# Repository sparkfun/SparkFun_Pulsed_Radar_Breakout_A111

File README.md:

SparkFun Pulsed Radar Breakout - A111
========================================

[*SparkFun A111 Pulsed Radar (SEN-16826)*](https://www.sparkfun.com/products/16826)

Does your project require high-precision, cutting-edge distance measurement? Or maybe speed-, motion-, or gesture-sensing? We’re not talking about simple ultrasonic, or even infrared, sensors here, but 60GHz radar! Well say hello to our tiny, pulsed-radar friend: the Acconeer A111.

The A111 is a single-chip solution for pulsed coherent radar (PCR). It comes complete with integrated antennae and an SPI interface capable of clock speeds of up to 50MHz. The A111’s primary use case is distance-sensing, but it also supports applications in gesture-, motion-, material-, and speed-detection. It can see objects at distances of up to two meters.

Our breakout board for the A111 includes a 1.8V regulator, voltage-level translation between 1.8V and 5V, and, of course, it breaks out all pins of the pulsed radar sensor to both 0.1-inch and Raspberry Pi-friendly headers.

The breakout board is primarily **designed to interface directly with a Raspberry Pi** – Acconeer’s SDK currently only supports ARMv7’s (e.g. a Pi) and ARM Cortex-M4’s. Check out our <a href="https://learn.sparkfun.com/tutorials/getting-started-with-the-a111-pulsed-radar-sensor">Getting Started with the A111 Pulsed Radar Sensor tutorial</a>, which explains how to use the sensor with a Raspberry Pi.

SparkFun labored with love to create this board. Feel like supporting open source hardware? 
Buy a [breakout board](https://www.sparkfun.com/products/16826) from SparkFun!

Repository Contents
-------------------

* **/Documents** - Datasheets
* **/Hardware** - Eagle design files (.brd, .sch)
* **/Production** - Production panel files (.brd)

Documentation
-------------------
* Acconeer
  * **[Developer](https://developer.acconeer.com/)** - SW Download, datasheet, user guide, FAQ
* **[Acconeer Example Code](https://github.com/acconeer)**
* **[Example Code](https://github.com/sparkfun/SparkFun_Pulsed_Radar_A111_Example_Code)** - Archived repo that used to hold the SparkFun example code for the Pulsed Radar Breakout. Make sure to head over to Acconeer's website to download the latest! 
* **[Getting Started Guide](https://learn.sparkfun.com/tutorials/getting-started-with-the-a111-pulsed-radar-sensor)** - Basic hookup guide.

Product Versions
----------------
* [SEN-16826](https://www.sparkfun.com/products/16826) - v1.1
* [SEN-15577](https://www.sparkfun.com/products/15577) - v1.0

Version History
---------------
- v1.1
- [v1.0](https://github.com/sparkfun/SparkFun_Pulsed_Radar_Breakout_A111/releases/tag/v1.0) - initial release

License Information
-------------------

This product is _**open source**_! 

If you have any questions or concerns on licensing, please contact technical support on our [SparkFun forums](https://forum.sparkfun.com/viewforum.php?f=152).

Please use, reuse, and modify these files as you see fit. Please maintain attribution to SparkFun Electronics and release any derivative under the same license.

Distributed as-is; no warranty is given.

- Your friends at SparkFun.

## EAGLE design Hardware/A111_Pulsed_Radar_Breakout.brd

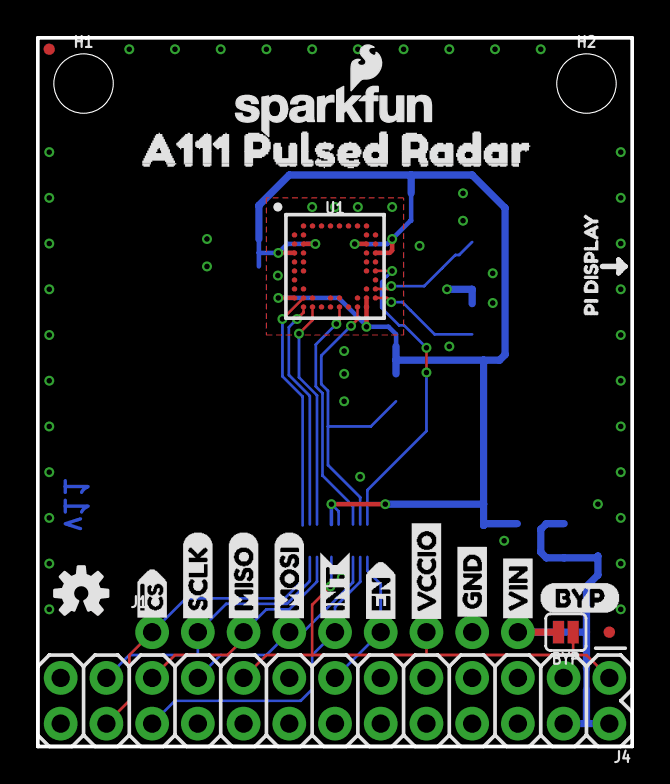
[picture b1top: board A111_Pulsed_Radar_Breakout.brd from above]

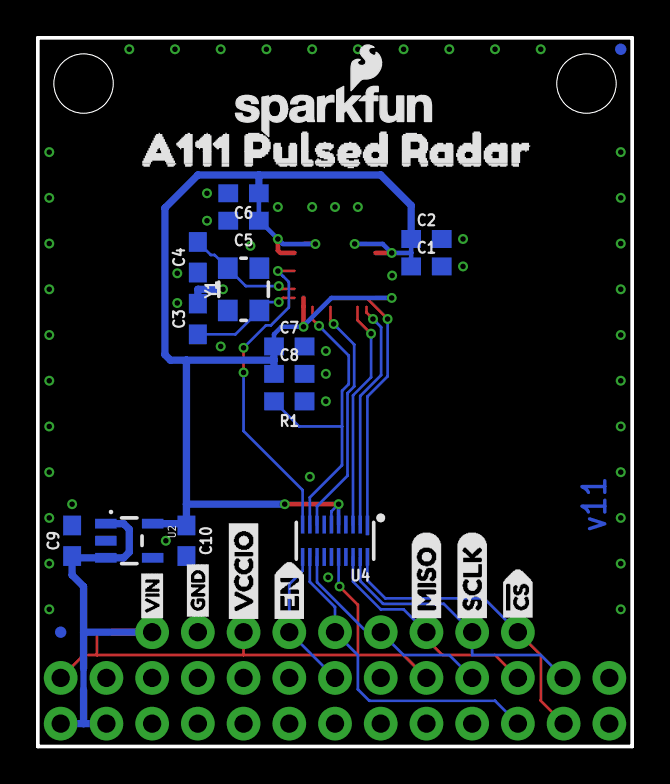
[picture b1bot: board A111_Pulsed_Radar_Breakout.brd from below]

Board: 2 copper layers, 33.0 x 39.4 mm, 48 parts (25 on the bottom side), 18 nets.

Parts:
BYP: JUMPER-SMT_2_NO_SILK; SMT-JUMPER_2_NO_SILK
C1, C5, C7: 0.1uF; 0603
C2, C6, C8, C9, C10: 1.0uF; 0603
C3, C4: 10pF; 0603
FD1, FD2, FD3, FD4: FIDUCIALUFIDUCIAL; FIDUCIAL-MICRO
FRAME1: FRAME-LETTER; CREATIVE_COMMONS
H1, H2: STAND-OFF
J1: 1X09_NO_SILK
J4: RASPBERRYPI-26-PIN-GPIO; 2X13
LOGO1, LOGO3: SFE_LOGO_NAME_FLAME.1_INCH; SFE_LOGO_NAME_FLAME_.1
LOGO2: OSHW-LOGOS; OSHW-LOGO-S
R1: 100k; 0603
U1: A111
U2: AP2127K-1.8V; SOT23-5
U4: TXB0108DQSR; UFDFN-20
U$1, U$9: A111_PULSED_RADAR9
U$2, U$10: SCLK3
U$3, U$11: MISO4
U$4: MOSI5
U$5: INT8
U$6, U$18: EN9
U$7: GND0
U$8: BYP
U$12: PI_DISPLAY9
U$13, U$17: #CS9
U$16: VIN0
U$19, U$20: VCCIO1
U$21: GND6
U$22: VIN5
Y1: 26MHz; CRYSTAL-SMD-3.2X2.5MM

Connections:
1.8V: C1.1, C2.1, C5.1, C6.1, C7.1, C8.1, C10.1, U1.C2, U1.C9, U1.D1, U1.D10, U1.J1, U1.J9, U1.K9, U2.5, U4.5, U4.6
!CS!: U1.J2, U4.1
!CS!_RPI: J1.1, J4.24, U4.20
ENABLE: U1.F10, U4.10
ENABLE_RPI: J1.6, J4.13, U4.11
GND: C1.2, C2.2, C3.2, C4.1, C5.2, C6.2, C7.2, C8.2, C9.2, C10.2, J1.8, J4.6, J4.9, J4.14, J4.20, J4.25, R1.1, U1.A3, U1.A4, U1.A5, U1.A6, U1.A7, U1.A8, U1.A9, U1.B2, U1.B9, U1.B10, U1.C1, U1.C10, U1.D2, U1.D9, U1.E1, U1.E2, U1.E9, U1.E10, U1.F1, U1.F2, U1.F9, U1.G1, U1.G10, U1.H1, U1.H2, U1.H9, U1.J3, U1.J5, U1.J6, U1.J8, U1.K4, U1.K5, U1.K7, U2.2, U4.15, Y1.2, Y1.4
INTERRUPT: R1.2, U1.K8, U4.9
INTERRUPT_RPI: J1.5, J4.22, U4.12
MISO: U1.K3, U4.3
MISO_RPI: J1.3, J4.21, U4.18
MOSI: U1.K6, U4.8
MOSI_RPI: J1.4, J4.19, U4.13
unnamed: C3.1, U1.J10, Y1.1
unnamed: C4.2, U1.H10, Y1.3
SCLK: U1.K2, U4.2
SCLK_RPI: J1.2, J4.23, U4.19
VCCIO: BYP.1, J1.7, J4.1, J4.17, U4.16
VIN: BYP.2, C9.1, J1.9, J4.2, J4.4, U2.1, U2.3

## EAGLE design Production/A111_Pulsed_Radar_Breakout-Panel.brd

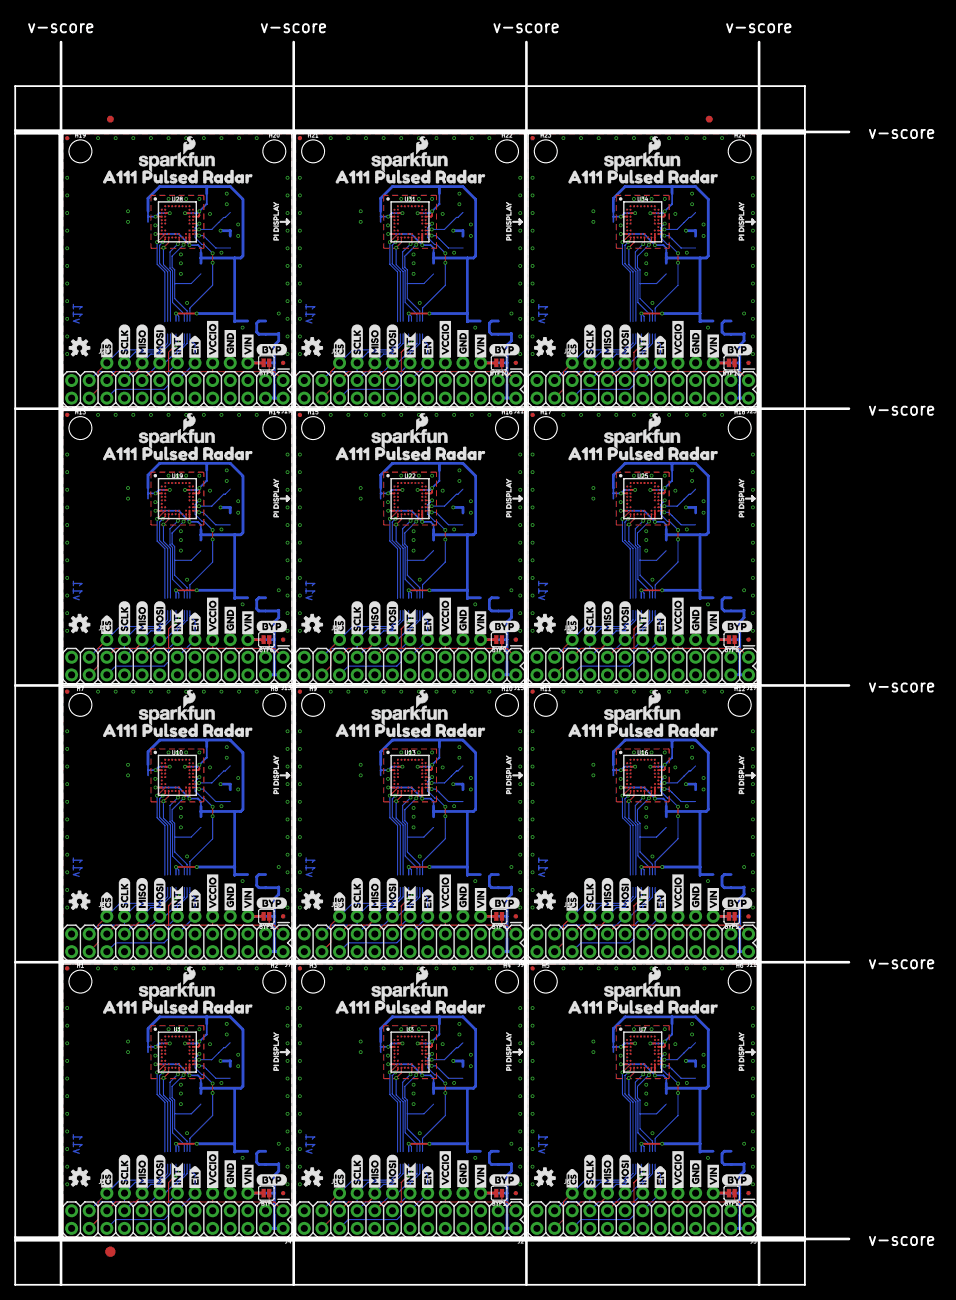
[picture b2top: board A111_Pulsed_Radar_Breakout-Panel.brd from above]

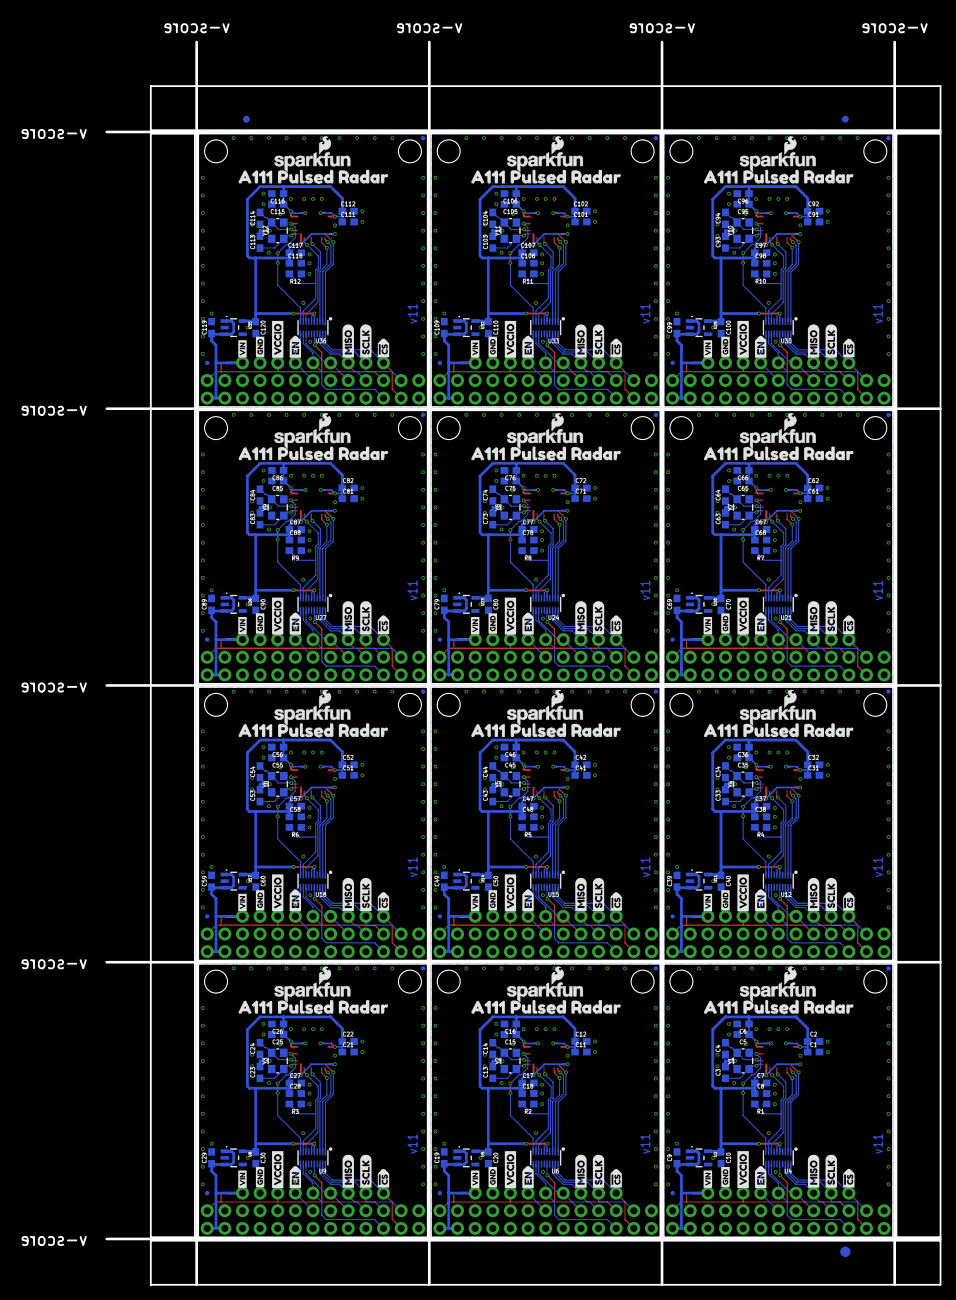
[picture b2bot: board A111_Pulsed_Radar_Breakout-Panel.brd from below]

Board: 2 copper layers, 133.3 x 182.9 mm, 570 parts (303 on the bottom side), 216 nets.

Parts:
BYP, BYP1, BYP2, BYP3, BYP4, BYP5, BYP6, BYP7, BYP8, BYP9, BYP10, BYP11: JUMPER-SMT_2_NO_SILK; SMT-JUMPER_2_NO_SILK
C1, C5, C7, C11, C15, C17, C21, C25, C27, C31, C35, C37, C41, C45, C47, C51, C55, C57, C61, C65, C67, C71, C75, C77, C81, C85, C87, C91, C95, C97, C101, C105, C107, C111, C115, C117: 0.1uF; 0603
C2, C6, C8, C9, C10, C12, C16, C18, C19, C20, C22, C26, C28, C29, C30, C32, C36, C38, C39, C40, C42, C46, C48, C49, C50, C52, C56, C58, C59, C60, C62, C66, C68, C69, C70, C72, C76, C78, C79, C80, C82, C86, C88, C89, C90, C92, C96, C98, C99, C100, C102, C106, C108, C109, C110, C112, C116, C118, C119, C120: 1.0uF; 0603
C3, C4, C13, C14, C23, C24, C33, C34, C43, C44, C53, C54, C63, C64, C73, C74, C83, C84, C93, C94, C103, C104, C113, C114: 10pF; 0603
E$1, E$2, E$3, E$4: FIDUCIAL-1X2
E$5, E$6: FIDUCIAL-1.5X3
FD1, FD2, FD3, FD4, FD5, FD6, FD7, FD8, FD9, FD10, FD11, FD12, FD13, FD14, FD15, FD16, FD17, FD18, FD19, FD20, FD21, FD22, FD23, FD24, FD25, FD26, FD27, FD28, FD29, FD30, FD31, FD32, FD33, FD34, FD35, FD36, FD37, FD38, FD39, FD40, FD41, FD42, FD43, FD44, FD45, FD46, FD47, FD48: FIDUCIALUFIDUCIAL; FIDUCIAL-MICRO
H1, H2, H3, H4, H5, H6, H7, H8, H9, H10, H11, H12, H13, H14, H15, H16, H17, H18, H19, H20, H21, H22, H23, H24: STAND-OFF
J1, J3, J6, J8, J10, J12, J14, J16, J18, J20, J22, J24: 1X09_NO_SILK
J2, J4, J5, J7, J9, J11, J13, J15, J17, J19, J21, J23: RASPBERRYPI-26-PIN-GPIO; 2X13
LOGO1, LOGO3, LOGO5, LOGO6, LOGO8, LOGO9, LOGO11, LOGO12, LOGO14, LOGO15, LOGO17, LOGO18, LOGO20, LOGO21, LOGO23, LOGO24, LOGO26, LOGO27, LOGO29, LOGO30, LOGO32, LOGO33, LOGO35, LOGO36: SFE_LOGO_NAME_FLAME.1_INCH; SFE_LOGO_NAME_FLAME_.1
LOGO2, LOGO4, LOGO7, LOGO10, LOGO13, LOGO16, LOGO19, LOGO22, LOGO25, LOGO28, LOGO31, LOGO34: OSHW-LOGOS; OSHW-LOGO-S
R1, R2, R3, R4, R5, R6, R7, R8, R9, R10, R11, R12: 100k; 0603
U1, U3, U7, U10, U13, U16, U19, U22, U25, U28, U31, U34: A111
U2, U5, U8, U11, U14, U17, U20, U23, U26, U29, U32, U35: AP2127K-1.8V; SOT23-5
U4, U6, U9, U12, U15, U18, U21, U24, U27, U30, U33, U36: TXB0108DQSR; UFDFN-20
U$1, U$9, U$29, U$30, U$49, U$50, U$69, U$70, U$89, U$90, U$109, U$110, U$129, U$130, U$149, U$150, U$169, U$170, U$189, U$190, U$209, U$210, U$229, U$230: A111_PULSED_RADAR9
U$2, U$10, U$14, U$26, U$41, U$46, U$61, U$66, U$81, U$86, U$101, U$106, U$121, U$126, U$141, U$146, U$161, U$166, U$181, U$186, U$201, U$206, U$221, U$226: SCLK3
U$3, U$11, U$15, U$27, U$42, U$47, U$62, U$67, U$82, U$87, U$102, U$107, U$122, U$127, U$142, U$147, U$162, U$167, U$182, U$187, U$202, U$207, U$222, U$227: MISO4
U$4, U$23, U$43, U$63, U$83, U$103, U$123, U$143, U$163, U$183, U$203, U$223: MOSI5
U$5, U$24, U$44, U$64, U$84, U$104, U$124, U$144, U$164, U$184, U$204, U$224: INT8
U$6, U$18, U$33, U$34, U$53, U$54, U$73, U$74, U$93, U$94, U$113, U$114, U$133, U$134, U$153, U$154, U$173, U$174, U$193, U$194, U$213, U$214, U$233, U$234: EN9
U$7, U$25, U$45, U$65, U$85, U$105, U$125, U$145, U$165, U$185, U$205, U$225: GND0
U$8, U$35, U$55, U$75, U$95, U$115, U$135, U$155, U$175, U$195, U$215, U$235: BYP
U$12, U$31, U$51, U$71, U$91, U$111, U$131, U$151, U$171, U$191, U$211, U$231: PI_DISPLAY9
U$13, U$17, U$28, U$32, U$48, U$52, U$68, U$72, U$88, U$92, U$108, U$112, U$128, U$132, U$148, U$152, U$168, U$172, U$188, U$192, U$208, U$212, U$228, U$232: #CS9
U$16, U$36, U$56, U$76, U$96, U$116, U$136, U$156, U$176, U$196, U$216, U$236: VIN0
U$19, U$20, U$37, U$38, U$57, U$58, U$77, U$78, U$97, U$98, U$117, U$118, U$137, U$138, U$157, U$158, U$177, U$178, U$197, U$198, U$217, U$218, U$237, U$238: VCCIO1
U$21, U$40, U$60, U$80, U$100, U$120, U$140, U$160, U$180, U$200, U$220, U$240: GND6
U$22, U$39, U$59, U$79, U$99, U$119, U$139, U$159, U$179, U$199, U$219, U$239: VIN5
Y1, Y2, Y3, Y4, Y5, Y6, Y7, Y8, Y9, Y10, Y11, Y12: 26MHz; CRYSTAL-SMD-3.2X2.5MM

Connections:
1.8V: C1.1, C2.1, C5.1, C6.1, C7.1, C8.1, C10.1, U1.C2, U1.C9, U1.D1, U1.D10, U1.J1, U1.J9, U1.K9, U2.5, U4.5, U4.6
1.8V1: C11.1, C12.1, C15.1, C16.1, C17.1, C18.1, C20.1, U3.C2, U3.C9, U3.D1, U3.D10, U3.J1, U3.J9, U3.K9, U5.5, U6.5, U6.6
1.8V2: C21.1, C22.1, C25.1, C26.1, C27.1, C28.1, C30.1, U7.C2, U7.C9, U7.D1, U7.D10, U7.J1, U7.J9, U7.K9, U8.5, U9.5, U9.6
1.8V3: C31.1, C32.1, C35.1, C36.1, C37.1, C38.1, C40.1, U10.C2, U10.C9, U10.D1, U10.D10, U10.J1, U10.J9, U10.K9, U11.5, U12.5, U12.6
1.8V4: C41.1, C42.1, C45.1, C46.1, C47.1, C48.1, C50.1, U13.C2, U13.C9, U13.D1, U13.D10, U13.J1, U13.J9, U13.K9, U14.5, U15.5, U15.6
1.8V5: C51.1, C52.1, C55.1, C56.1, C57.1, C58.1, C60.1, U16.C2, U16.C9, U16.D1, U16.D10, U16.J1, U16.J9, U16.K9, U17.5, U18.5, U18.6
1.8V6: C61.1, C62.1, C65.1, C66.1, C67.1, C68.1, C70.1, U19.C2, U19.C9, U19.D1, U19.D10, U19.J1, U19.J9, U19.K9, U20.5, U21.5, U21.6
1.8V7: C71.1, C72.1, C75.1, C76.1, C77.1, C78.1, C80.1, U22.C2, U22.C9, U22.D1, U22.D10, U22.J1, U22.J9, U22.K9, U23.5, U24.5, U24.6
1.8V8: C81.1, C82.1, C85.1, C86.1, C87.1, C88.1, C90.1, U25.C2, U25.C9, U25.D1, U25.D10, U25.J1, U25.J9, U25.K9, U26.5, U27.5, U27.6
1.8V9: C91.1, C92.1, C95.1, C96.1, C97.1, C98.1, C100.1, U28.C2, U28.C9, U28.D1, U28.D10, U28.J1, U28.J9, U28.K9, U29.5, U30.5, U30.6
1.8V10: C101.1, C102.1, C105.1, C106.1, C107.1, C108.1, C110.1, U31.C2, U31.C9, U31.D1, U31.D10, U31.J1, U31.J9, U31.K9, U32.5, U33.5, U33.6
1.8V11: C111.1, C112.1, C115.1, C116.1, C117.1, C118.1, C120.1, U34.C2, U34.C9, U34.D1, U34.D10, U34.J1, U34.J9, U34.K9, U35.5, U36.5, U36.6
!CS!: U1.J2, U4.1
!CS!1: U3.J2, U6.1
!CS!2: U7.J2, U9.1
!CS!3: U10.J2, U12.1
!CS!4: U13.J2, U15.1
!CS!5: U16.J2, U18.1
!CS!6: U19.J2, U21.1
!CS!7: U22.J2, U24.1
!CS!8: U25.J2, U27.1
!CS!9: U28.J2, U30.1
!CS!10: U31.J2, U33.1
!CS!11: U34.J2, U36.1
!CS!_RPI: J1.1, J4.24, U4.20
!CS!_RPI1: J2.24, J3.1, U6.20
!CS!_RPI2: J5.24, J6.1, U9.20
!CS!_RPI3: J7.24, J8.1, U12.20
!CS!_RPI4: J9.24, J10.1, U15.20
!CS!_RPI5: J11.24, J12.1, U18.20
!CS!_RPI6: J13.24, J14.1, U21.20
!CS!_RPI7: J15.24, J16.1, U24.20
!CS!_RPI8: J17.24, J18.1, U27.20
!CS!_RPI9: J19.24, J20.1, U30.20
!CS!_RPI10: J21.24, J22.1, U33.20
!CS!_RPI11: J23.24, J24.1, U36.20
ENABLE: U1.F10, U4.10
ENABLE1: U3.F10, U6.10
ENABLE2: U7.F10, U9.10
ENABLE3: U10.F10, U12.10
ENABLE4: U13.F10, U15.10
ENABLE5: U16.F10, U18.10
ENABLE6: U19.F10, U21.10
ENABLE7: U22.F10, U24.10
ENABLE8: U25.F10, U27.10
ENABLE9: U28.F10, U30.10
ENABLE10: U31.F10, U33.10
ENABLE11: U34.F10, U36.10
ENABLE_RPI: J1.6, J4.13, U4.11
ENABLE_RPI1: J2.13, J3.6, U6.11
ENABLE_RPI2: J5.13, J6.6, U9.11
ENABLE_RPI3: J7.13, J8.6, U12.11
ENABLE_RPI4: J9.13, J10.6, U15.11
ENABLE_RPI5: J11.13, J12.6, U18.11
ENABLE_RPI6: J13.13, J14.6, U21.11
ENABLE_RPI7: J15.13, J16.6, U24.11
ENABLE_RPI8: J17.13, J18.6, U27.11
ENABLE_RPI9: J19.13, J20.6, U30.11
ENABLE_RPI10: J21.13, J22.6, U33.11
ENABLE_RPI11: J23.13, J24.6, U36.11
GND: C1.2, C2.2, C3.2, C4.1, C5.2, C6.2, C7.2, C8.2, C9.2, C10.2, J1.8, J4.6, J4.9, J4.14, J4.20, J4.25, R1.1, U1.A3, U1.A4, U1.A5, U1.A6, U1.A7, U1.A8, U1.A9, U1.B2, U1.B9, U1.B10, U1.C1, U1.C10, U1.D2, U1.D9, U1.E1, U1.E2, U1.E9, U1.E10, U1.F1, U1.F2, U1.F9, U1.G1, U1.G10, U1.H1, U1.H2, U1.H9, U1.J3, U1.J5, U1.J6, U1.J8, U1.K4, U1.K5, U1.K7, U2.2, U4.15, Y1.2, Y1.4
GND1: C11.2, C12.2, C13.2, C14.1, C15.2, C16.2, C17.2, C18.2, C19.2, C20.2, J2.6, J2.9, J2.14, J2.20, J2.25, J3.8, R2.1, U3.A3, U3.A4, U3.A5, U3.A6, U3.A7, U3.A8, U3.A9, U3.B2, U3.B9, U3.B10, U3.C1, U3.C10, U3.D2, U3.D9, U3.E1, U3.E2, U3.E9, U3.E10, U3.F1, U3.F2, U3.F9, U3.G1, U3.G10, U3.H1, U3.H2, U3.H9, U3.J3, U3.J5, U3.J6, U3.J8, U3.K4, U3.K5, U3.K7, U5.2, U6.15, Y2.2, Y2.4
GND2: C21.2, C22.2, C23.2, C24.1, C25.2, C26.2, C27.2, C28.2, C29.2, C30.2, J5.6, J5.9, J5.14, J5.20, J5.25, J6.8, R3.1, U7.A3, U7.A4, U7.A5, U7.A6, U7.A7, U7.A8, U7.A9, U7.B2, U7.B9, U7.B10, U7.C1, U7.C10, U7.D2, U7.D9, U7.E1, U7.E2, U7.E9, U7.E10, U7.F1, U7.F2, U7.F9, U7.G1, U7.G10, U7.H1, U7.H2, U7.H9, U7.J3, U7.J5, U7.J6, U7.J8, U7.K4, U7.K5, U7.K7, U8.2, U9.15, Y3.2, Y3.4
GND3: C31.2, C32.2, C33.2, C34.1, C35.2, C36.2, C37.2, C38.2, C39.2, C40.2, J7.6, J7.9, J7.14, J7.20, J7.25, J8.8, R4.1, U10.A3, U10.A4, U10.A5, U10.A6, U10.A7, U10.A8, U10.A9, U10.B2, U10.B9, U10.B10, U10.C1, U10.C10, U10.D2, U10.D9, U10.E1, U10.E2, U10.E9, U10.E10, U10.F1, U10.F2, U10.F9, U10.G1, U10.G10, U10.H1, U10.H2, U10.H9, U10.J3, U10.J5, U10.J6, U10.J8, U10.K4, U10.K5, U10.K7, U11.2, U12.15, Y4.2, Y4.4
GND4: C41.2, C42.2, C43.2, C44.1, C45.2, C46.2, C47.2, C48.2, C49.2, C50.2, J9.6, J9.9, J9.14, J9.20, J9.25, J10.8, R5.1, U13.A3, U13.A4, U13.A5, U13.A6, U13.A7, U13.A8, U13.A9, U13.B2, U13.B9, U13.B10, U13.C1, U13.C10, U13.D2, U13.D9, U13.E1, U13.E2, U13.E9, U13.E10, U13.F1, U13.F2, U13.F9, U13.G1, U13.G10, U13.H1, U13.H2, U13.H9, U13.J3, U13.J5, U13.J6, U13.J8, U13.K4, U13.K5, U13.K7, U14.2, U15.15, Y5.2, Y5.4
GND5: C51.2, C52.2, C53.2, C54.1, C55.2, C56.2, C57.2, C58.2, C59.2, C60.2, J11.6, J11.9, J11.14, J11.20, J11.25, J12.8, R6.1, U16.A3, U16.A4, U16.A5, U16.A6, U16.A7, U16.A8, U16.A9, U16.B2, U16.B9, U16.B10, U16.C1, U16.C10, U16.D2, U16.D9, U16.E1, U16.E2, U16.E9, U16.E10, U16.F1, U16.F2, U16.F9, U16.G1, U16.G10, U16.H1, U16.H2, U16.H9, U16.J3, U16.J5, U16.J6, U16.J8, U16.K4, U16.K5, U16.K7, U17.2, U18.15, Y6.2, Y6.4
GND6: C61.2, C62.2, C63.2, C64.1, C65.2, C66.2, C67.2, C68.2, C69.2, C70.2, J13.6, J13.9, J13.14, J13.20, J13.25, J14.8, R7.1, U19.A3, U19.A4, U19.A5, U19.A6, U19.A7, U19.A8, U19.A9, U19.B2, U19.B9, U19.B10, U19.C1, U19.C10, U19.D2, U19.D9, U19.E1, U19.E2, U19.E9, U19.E10, U19.F1, U19.F2, U19.F9, U19.G1, U19.G10, U19.H1, U19.H2, U19.H9, U19.J3, U19.J5, U19.J6, U19.J8, U19.K4, U19.K5, U19.K7, U20.2, U21.15, Y7.2, Y7.4
GND7: C71.2, C72.2, C73.2, C74.1, C75.2, C76.2, C77.2, C78.2, C79.2, C80.2, J15.6, J15.9, J15.14, J15.20, J15.25, J16.8, R8.1, U22.A3, U22.A4, U22.A5, U22.A6, U22.A7, U22.A8, U22.A9, U22.B2, U22.B9, U22.B10, U22.C1, U22.C10, U22.D2, U22.D9, U22.E1, U22.E2, U22.E9, U22.E10, U22.F1, U22.F2, U22.F9, U22.G1, U22.G10, U22.H1, U22.H2, U22.H9, U22.J3, U22.J5, U22.J6, U22.J8, U22.K4, U22.K5, U22.K7, U23.2, U24.15, Y8.2, Y8.4
GND8: C81.2, C82.2, C83.2, C84.1, C85.2, C86.2, C87.2, C88.2, C89.2, C90.2, J17.6, J17.9, J17.14, J17.20, J17.25, J18.8, R9.1, U25.A3, U25.A4, U25.A5, U25.A6, U25.A7, U25.A8, U25.A9, U25.B2, U25.B9, U25.B10, U25.C1, U25.C10, U25.D2, U25.D9, U25.E1, U25.E2, U25.E9, U25.E10, U25.F1, U25.F2, U25.F9, U25.G1, U25.G10, U25.H1, U25.H2, U25.H9, U25.J3, U25.J5, U25.J6, U25.J8, U25.K4, U25.K5, U25.K7, U26.2, U27.15, Y9.2, Y9.4
GND9: C91.2, C92.2, C93.2, C94.1, C95.2, C96.2, C97.2, C98.2, C99.2, C100.2, J19.6, J19.9, J19.14, J19.20, J19.25, J20.8, R10.1, U28.A3, U28.A4, U28.A5, U28.A6, U28.A7, U28.A8, U28.A9, U28.B2, U28.B9, U28.B10, U28.C1, U28.C10, U28.D2, U28.D9, U28.E1, U28.E2, U28.E9, U28.E10, U28.F1, U28.F2, U28.F9, U28.G1, U28.G10, U28.H1, U28.H2, U28.H9, U28.J3, U28.J5, U28.J6, U28.J8, U28.K4, U28.K5, U28.K7, U29.2, U30.15, Y10.2, Y10.4
GND10: C101.2, C102.2, C103.2, C104.1, C105.2, C106.2, C107.2, C108.2, C109.2, C110.2, J21.6, J21.9, J21.14, J21.20, J21.25, J22.8, R11.1, U31.A3, U31.A4, U31.A5, U31.A6, U31.A7, U31.A8, U31.A9, U31.B2, U31.B9, U31.B10, U31.C1, U31.C10, U31.D2, U31.D9, U31.E1, U31.E2, U31.E9, U31.E10, U31.F1, U31.F2, U31.F9, U31.G1, U31.G10, U31.H1, U31.H2, U31.H9, U31.J3, U31.J5, U31.J6, U31.J8, U31.K4, U31.K5, U31.K7, U32.2, U33.15, Y11.2, Y11.4
GND11: C111.2, C112.2, C113.2, C114.1, C115.2, C116.2, C117.2, C118.2, C119.2, C120.2, J23.6, J23.9, J23.14, J23.20, J23.25, J24.8, R12.1, U34.A3, U34.A4, U34.A5, U34.A6, U34.A7, U34.A8, U34.A9, U34.B2, U34.B9, U34.B10, U34.C1, U34.C10, U34.D2, U34.D9, U34.E1, U34.E2, U34.E9, U34.E10, U34.F1, U34.F2, U34.F9, U34.G1, U34.G10, U34.H1, U34.H2, U34.H9, U34.J3, U34.J5, U34.J6, U34.J8, U34.K4, U34.K5, U34.K7, U35.2, U36.15, Y12.2, Y12.4
INTERRUPT: R1.2, U1.K8, U4.9
INTERRUPT1: R2.2, U3.K8, U6.9
INTERRUPT2: R3.2, U7.K8, U9.9
INTERRUPT3: R4.2, U10.K8, U12.9
INTERRUPT4: R5.2, U13.K8, U15.9
INTERRUPT5: R6.2, U16.K8, U18.9
INTERRUPT6: R7.2, U19.K8, U21.9
INTERRUPT7: R8.2, U22.K8, U24.9
INTERRUPT8: R9.2, U25.K8, U27.9
INTERRUPT9: R10.2, U28.K8, U30.9
INTERRUPT10: R11.2, U31.K8, U33.9
INTERRUPT11: R12.2, U34.K8, U36.9
INTERRUPT_RPI: J1.5, J4.22, U4.12
INTERRUPT_RPI1: J2.22, J3.5, U6.12
INTERRUPT_RPI2: J5.22, J6.5, U9.12
INTERRUPT_RPI3: J7.22, J8.5, U12.12
INTERRUPT_RPI4: J9.22, J10.5, U15.12
INTERRUPT_RPI5: J11.22, J12.5, U18.12
INTERRUPT_RPI6: J13.22, J14.5, U21.12
INTERRUPT_RPI7: J15.22, J16.5, U24.12
INTERRUPT_RPI8: J17.22, J18.5, U27.12
INTERRUPT_RPI9: J19.22, J20.5, U30.12
INTERRUPT_RPI10: J21.22, J22.5, U33.12
INTERRUPT_RPI11: J23.22, J24.5, U36.12
MISO: U1.K3, U4.3
MISO1: U3.K3, U6.3
MISO2: U7.K3, U9.3
MISO3: U10.K3, U12.3
MISO4: U13.K3, U15.3
MISO5: U16.K3, U18.3
MISO6: U19.K3, U21.3
MISO7: U22.K3, U24.3
MISO8: U25.K3, U27.3
MISO9: U28.K3, U30.3
MISO10: U31.K3, U33.3
MISO11: U34.K3, U36.3
MISO_RPI: J1.3, J4.21, U4.18
MISO_RPI1: J2.21, J3.3, U6.18
MISO_RPI2: J5.21, J6.3, U9.18
MISO_RPI3: J7.21, J8.3, U12.18
MISO_RPI4: J9.21, J10.3, U15.18
MISO_RPI5: J11.21, J12.3, U18.18
MISO_RPI6: J13.21, J14.3, U21.18
MISO_RPI7: J15.21, J16.3, U24.18
MISO_RPI8: J17.21, J18.3, U27.18
MISO_RPI9: J19.21, J20.3, U30.18
MISO_RPI10: J21.21, J22.3, U33.18
MISO_RPI11: J23.21, J24.3, U36.18
MOSI: U1.K6, U4.8
MOSI1: U3.K6, U6.8
MOSI2: U7.K6, U9.8
MOSI3: U10.K6, U12.8
MOSI4: U13.K6, U15.8
MOSI5: U16.K6, U18.8
MOSI6: U19.K6, U21.8
MOSI7: U22.K6, U24.8
MOSI8: U25.K6, U27.8
MOSI9: U28.K6, U30.8
MOSI10: U31.K6, U33.8
MOSI11: U34.K6, U36.8
MOSI_RPI: J1.4, J4.19, U4.13
MOSI_RPI1: J2.19, J3.4, U6.13
MOSI_RPI2: J5.19, J6.4, U9.13
MOSI_RPI3: J7.19, J8.4, U12.13
MOSI_RPI4: J9.19, J10.4, U15.13
MOSI_RPI5: J11.19, J12.4, U18.13
MOSI_RPI6: J13.19, J14.4, U21.13
MOSI_RPI7: J15.19, J16.4, U24.13
MOSI_RPI8: J17.19, J18.4, U27.13
MOSI_RPI9: J19.19, J20.4, U30.13
MOSI_RPI10: J21.19, J22.4, U33.13
MOSI_RPI11: J23.19, J24.4, U36.13
unnamed: C3.1, U1.J10, Y1.1
unnamed: C4.2, U1.H10, Y1.3
unnamed: C13.1, U3.J10, Y2.1
unnamed: C14.2, U3.H10, Y2.3
unnamed: C23.1, U7.J10, Y3.1
unnamed: C24.2, U7.H10, Y3.3
unnamed: C33.1, U10.J10, Y4.1
unnamed: C34.2, U10.H10, Y4.3
unnamed: C43.1, U13.J10, Y5.1
unnamed: C44.2, U13.H10, Y5.3
unnamed: C53.1, U16.J10, Y6.1
unnamed: C54.2, U16.H10, Y6.3
unnamed: C63.1, U19.J10, Y7.1
unnamed: C64.2, U19.H10, Y7.3
unnamed: C73.1, U22.J10, Y8.1
unnamed: C74.2, U22.H10, Y8.3
unnamed: C83.1, U25.J10, Y9.1
unnamed: C84.2, U25.H10, Y9.3
unnamed: C93.1, U28.J10, Y10.1
unnamed: C94.2, U28.H10, Y10.3
unnamed: C103.1, U31.J10, Y11.1
unnamed: C104.2, U31.H10, Y11.3
unnamed: C113.1, U34.J10, Y12.1
unnamed: C114.2, U34.H10, Y12.3
SCLK: U1.K2, U4.2
SCLK1: U3.K2, U6.2
SCLK2: U7.K2, U9.2
SCLK3: U10.K2, U12.2
SCLK4: U13.K2, U15.2
SCLK5: U16.K2, U18.2
SCLK6: U19.K2, U21.2
SCLK7: U22.K2, U24.2
SCLK8: U25.K2, U27.2
SCLK9: U28.K2, U30.2
SCLK10: U31.K2, U33.2
SCLK11: U34.K2, U36.2
SCLK_RPI: J1.2, J4.23, U4.19
SCLK_RPI1: J2.23, J3.2, U6.19
SCLK_RPI2: J5.23, J6.2, U9.19
SCLK_RPI3: J7.23, J8.2, U12.19
SCLK_RPI4: J9.23, J10.2, U15.19
SCLK_RPI5: J11.23, J12.2, U18.19
SCLK_RPI6: J13.23, J14.2, U21.19
SCLK_RPI7: J15.23, J16.2, U24.19
SCLK_RPI8: J17.23, J18.2, U27.19
SCLK_RPI9: J19.23, J20.2, U30.19
SCLK_RPI10: J21.23, J22.2, U33.19
SCLK_RPI11: J23.23, J24.2, U36.19
VCCIO: BYP.1, J1.7, J4.1, J4.17, U4.16
VCCIO1: BYP1.1, J2.1, J2.17, J3.7, U6.16
VCCIO2: BYP2.1, J5.1, J5.17, J6.7, U9.16
VCCIO3: BYP3.1, J7.1, J7.17, J8.7, U12.16
VCCIO4: BYP4.1, J9.1, J9.17, J10.7, U15.16
VCCIO5: BYP5.1, J11.1, J11.17, J12.7, U18.16
VCCIO6: BYP6.1, J13.1, J13.17, J14.7, U21.16
VCCIO7: BYP7.1, J15.1, J15.17, J16.7, U24.16
VCCIO8: BYP8.1, J17.1, J17.17, J18.7, U27.16
VCCIO9: BYP9.1, J19.1, J19.17, J20.7, U30.16
VCCIO10: BYP10.1, J21.1, J21.17, J22.7, U33.16
VCCIO11: BYP11.1, J23.1, J23.17, J24.7, U36.16
VIN: BYP.2, C9.1, J1.9, J4.2, J4.4, U2.1, U2.3
VIN1: BYP1.2, C19.1, J2.2, J2.4, J3.9, U5.1, U5.3
VIN2: BYP2.2, C29.1, J5.2, J5.4, J6.9, U8.1, U8.3
VIN3: BYP3.2, C39.1, J7.2, J7.4, J8.9, U11.1, U11.3
VIN4: BYP4.2, C49.1, J9.2, J9.4, J10.9, U14.1, U14.3
VIN5: BYP5.2, C59.1, J11.2, J11.4, J12.9, U17.1, U17.3
VIN6: BYP6.2, C69.1, J13.2, J13.4, J14.9, U20.1, U20.3
VIN7: BYP7.2, C79.1, J15.2, J15.4, J16.9, U23.1, U23.3
VIN8: BYP8.2, C89.1, J17.2, J17.4, J18.9, U26.1, U26.3
VIN9: BYP9.2, C99.1, J19.2, J19.4, J20.9, U29.1, U29.3
VIN10: BYP10.2, C109.1, J21.2, J21.4, J22.9, U32.1, U32.3
VIN11: BYP11.2, C119.1, J23.2, J23.4, J24.9, U35.1, U35.3

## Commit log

2019-07-30 Updates name in README
2019-08-05 Adds SparkFun logo to the underside, migrates all parts to SparkFun libraries.
2019-08-05 Updates A111 with SKU
2019-08-06 Replaces SparkFun silk with SparkFun silk with flame, grounds, 1.8V voltage regulator
2019-08-08 Changes DRC to SparkFun Fab Limit
2019-08-08 Adds Production Files
2019-08-08 Fixes proportional text in schematic
2019-08-08 Updates schematic with VCC range, updates silk on A111 part
2019-08-08 Updates silk once more
2019-08-08 Repanelizes after silk change
2019-09-24 Board Dimensions
    - Update measures layer
    - Include board dimensions
2019-12-20 Update README.md
    The logic level converter is tied directly to 5V
2020-05-06 Remove Examples
    Acconeer would like to handle the examples on their website since they provide frequent updates to the SDK. The examples are removed to avoid confusion.
2020-05-07 Splits power to level translation so that it's at on a separate power bus (3.3V on Rasp Pi)
2020-06-03 Updates the panel

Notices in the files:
parts and their libraries:
SparkFun-Aesthetics: Licensing: Creative Commons ShareAlike 4.0 International - https://creativecommons.org/licenses/by-sa/4.0
SparkFun-Aesthetics: Released under the Creative Commons Attribution Share-Alike 4.0 License
SparkFun-Aesthetics: https://creativecommons.org/licenses/by-sa/4.0
